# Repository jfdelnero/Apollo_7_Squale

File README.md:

Apollo 7 Squale toolchain and demos  
(c) 2015-2019 Jean-François DEL NERO  
(c) 2015-2019 Association MO5.COM ( [https://mo5.com](https://mo5.com) )
---

gcc6809 based Apollo 7 Squale C toolchain and demos examples

[Squale computer technical page](http://hxc2001.free.fr/Squale/index.html)

[Squale Demo release news letter](http://mag.mo5.com/actu/172742/mo5-com-presente-la-toute-premiere-demo-sur-squale)

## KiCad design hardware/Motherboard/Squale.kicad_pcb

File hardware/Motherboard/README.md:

Apollo 7 Squale Schematic and PCB 
---

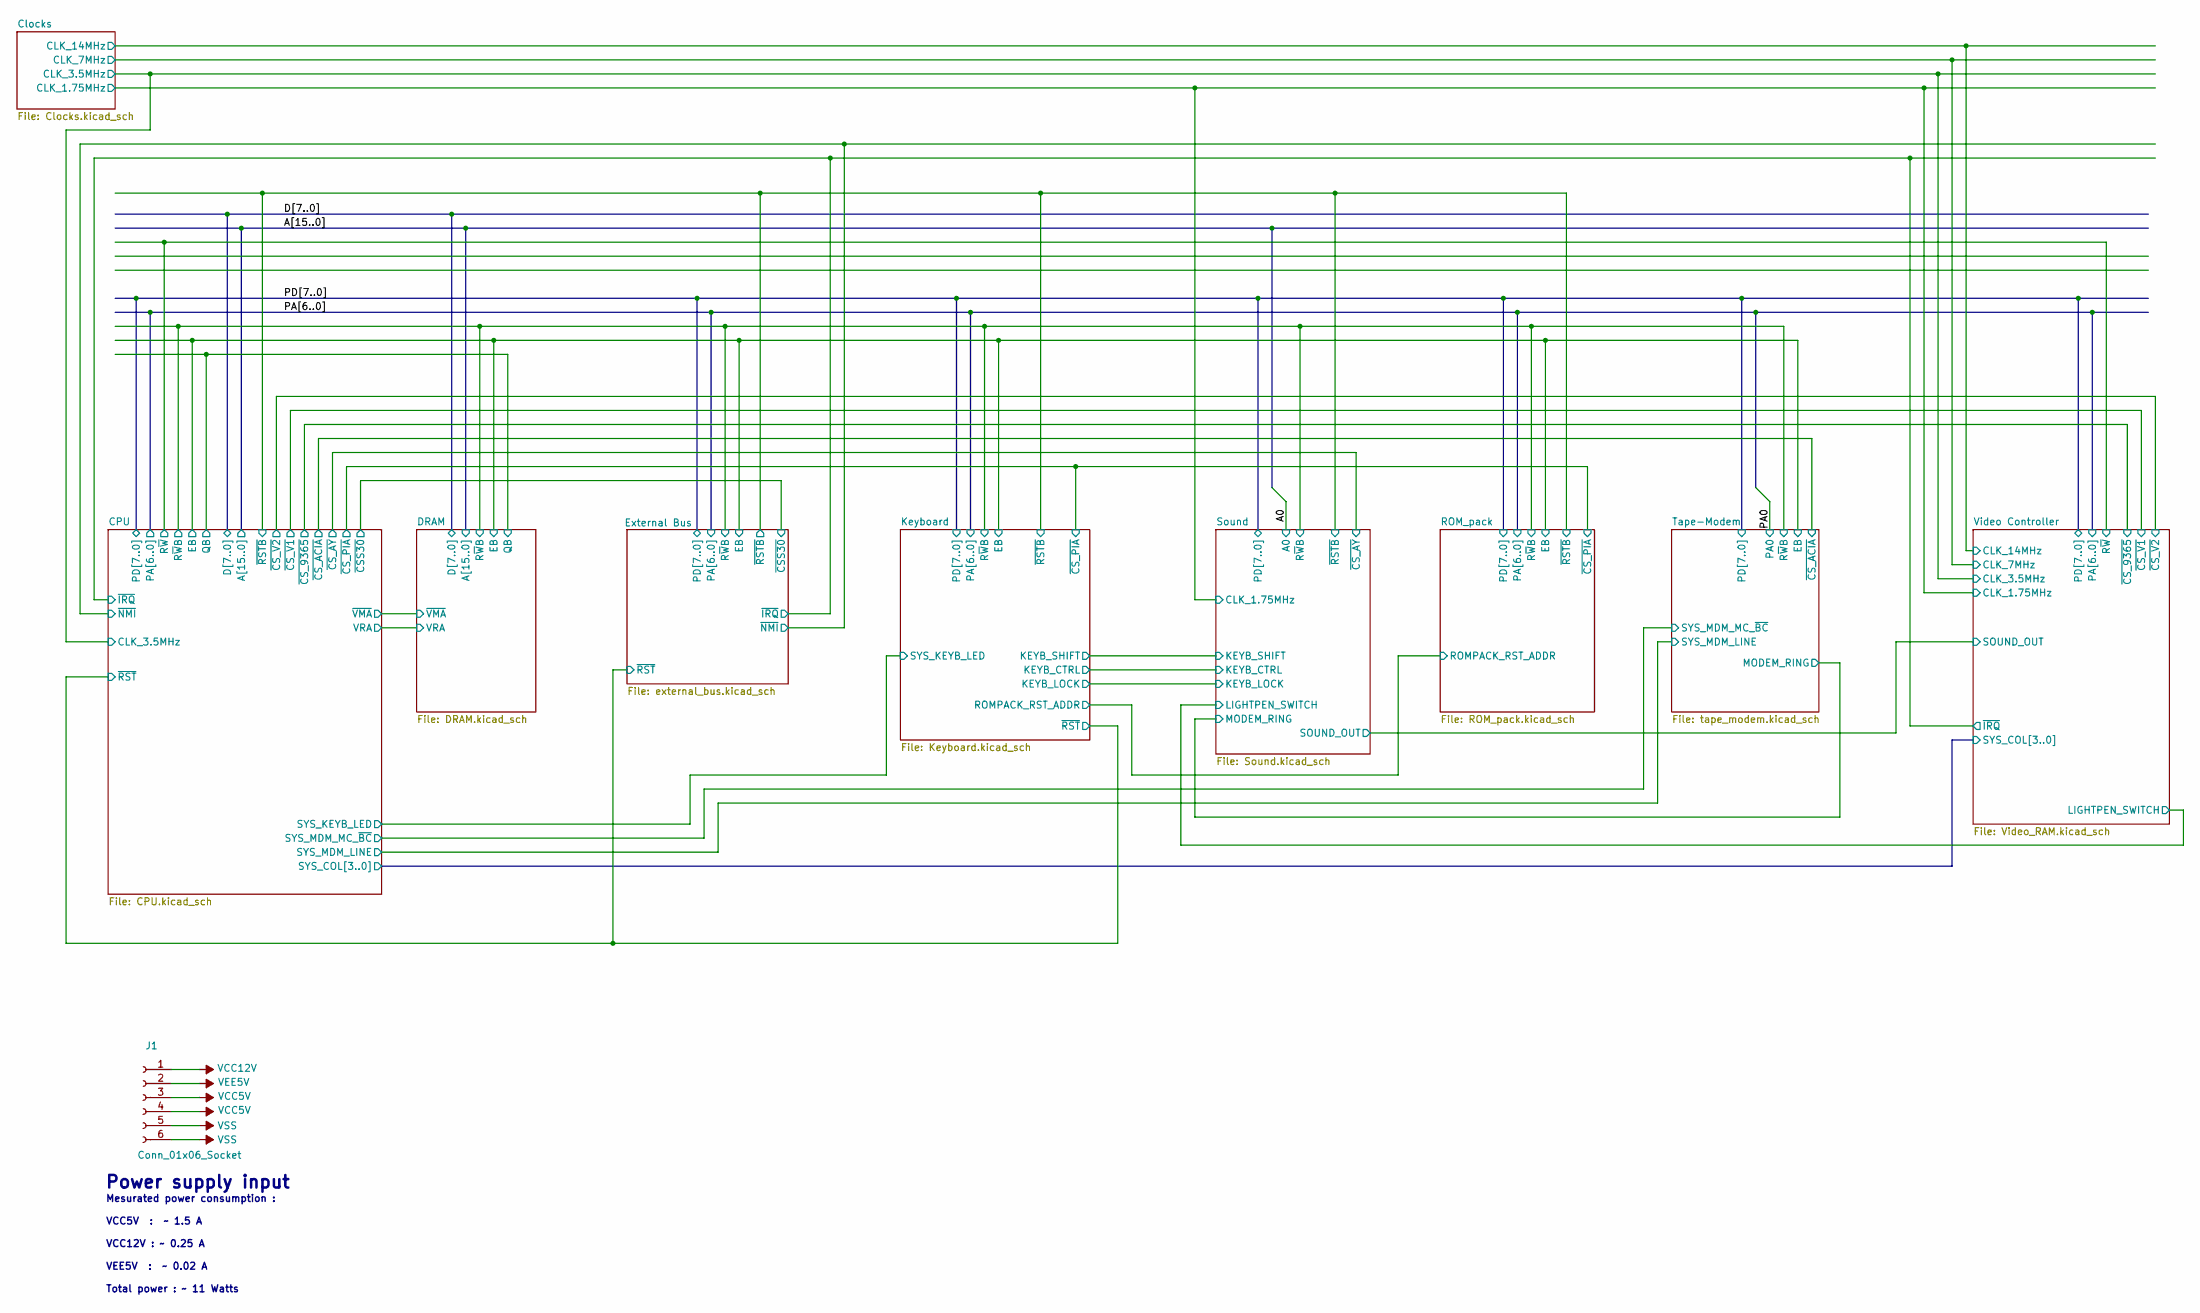
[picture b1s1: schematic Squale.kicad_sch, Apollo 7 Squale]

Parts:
J1: Conn_01x06_Socket; TerminalBlock_CUI_TB007-508-06_1x06_P5.08mm_Horizontal

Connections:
VCC5V: J1.3, J1.4; also elsewhere on the board
VCC12V: J1.1; also elsewhere on the board
VEE5V: J1.2; also elsewhere on the board
VSS: J1.5, J1.6; also elsewhere on the board

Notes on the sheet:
Power supply input
Mesurated power consumption : VCC5V : ~ 1.5 A VCC12V : ~ 0.25 A VEE5V : ~ 0.02 A Total power : ~ 11 Watts

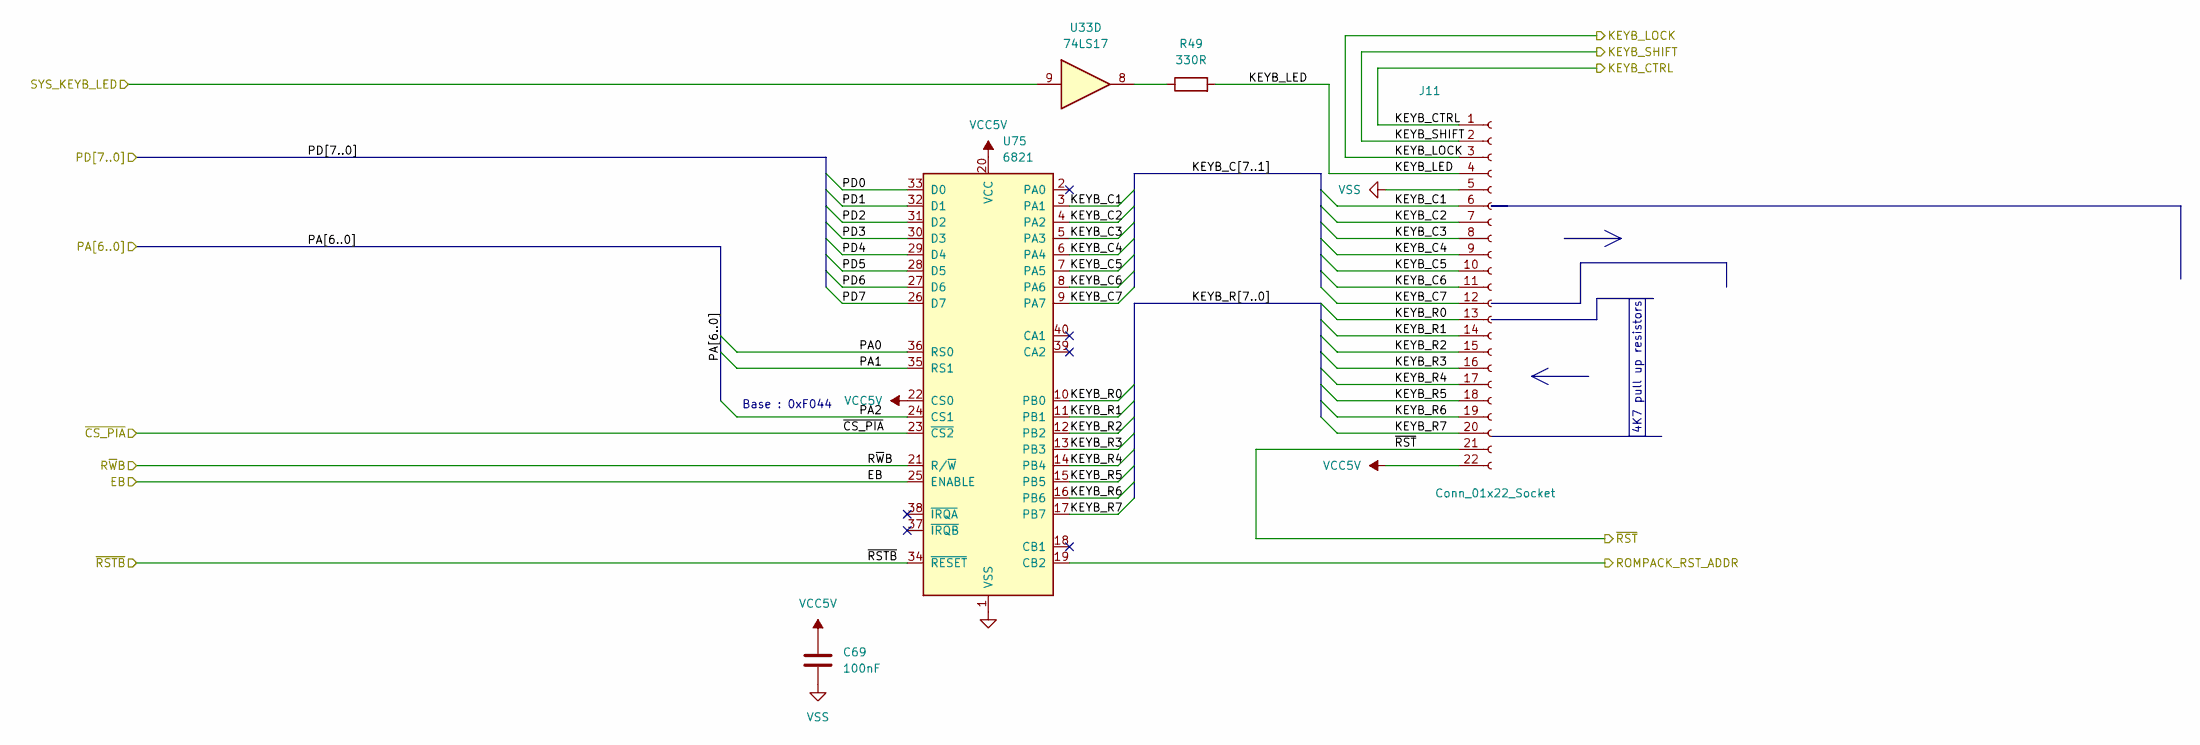
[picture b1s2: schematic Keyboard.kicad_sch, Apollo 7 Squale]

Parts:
C69: 100nF; C_Disc_D9.0mm_W2.5mm_P5.00mm
J11: Conn_01x22_Socket; PinHeader_1x22_P2.54mm_Vertical
R49: 330R; R_Axial_DIN0309_L9.0mm_D3.2mm_P12.70mm_Horizontal
U33: 74LS17; DIP-14_W7.62mm_Socket
U75: 6821; DIP-40_W15.24mm_Socket

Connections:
/CPU/EB: U75.25 (ENABLE); also elsewhere on the board
/CPU/R~WB: U75.21 (R/~W); also elsewhere on the board
/CPU/SYS_KEYB_LED: U33.9; also elsewhere on the board
/CPU/~CS_PIA: U75.23 (~CS2); also elsewhere on the board
/CPU/~RST: J11.21; also elsewhere on the board
/Keyboard/KEYB_C1: J11.6, U75.3 (PA1)
/Keyboard/KEYB_C2: J11.7, U75.4 (PA2)
/Keyboard/KEYB_C3: J11.8, U75.5 (PA3)
/Keyboard/KEYB_C4: J11.9, U75.6 (PA4)
/Keyboard/KEYB_C5: J11.10, U75.7 (PA5)
/Keyboard/KEYB_C6: J11.11, U75.8 (PA6)
/Keyboard/KEYB_C7: J11.12, U75.9 (PA7)
/Keyboard/KEYB_CTRL: J11.1; also elsewhere on the board
/Keyboard/KEYB_LED: J11.4, R49.2
/Keyboard/KEYB_LOCK: J11.3; also elsewhere on the board
/Keyboard/KEYB_R0: J11.13, U75.10 (PB0)
/Keyboard/KEYB_R1: J11.14, U75.11 (PB1)
/Keyboard/KEYB_R2: J11.15, U75.12 (PB2)
/Keyboard/KEYB_R3: J11.16, U75.13 (PB3)
/Keyboard/KEYB_R4: J11.17, U75.14 (PB4)
/Keyboard/KEYB_R5: J11.18, U75.15 (PB5)
/Keyboard/KEYB_R6: J11.19, U75.16 (PB6)
/Keyboard/KEYB_R7: J11.20, U75.17 (PB7)
/Keyboard/KEYB_SHIFT: J11.2; also elsewhere on the board
/Keyboard/ROMPACK_RST_ADDR: U75.19 (CB2); also elsewhere on the board
/Keyboard/~RSTB: U75.34 (~RESET); also elsewhere on the board
/PA0: U75.36 (RS0); also elsewhere on the board
/PA1: U75.35 (RS1); also elsewhere on the board
/PA2: U75.24 (CS1); also elsewhere on the board
/PD0: U75.33 (D0); also elsewhere on the board
/PD1: U75.32 (D1); also elsewhere on the board
/PD2: U75.31 (D2); also elsewhere on the board
/PD3: U75.30 (D3); also elsewhere on the board
/PD4: U75.29 (D4); also elsewhere on the board
/PD5: U75.28 (D5); also elsewhere on the board
/PD6: U75.27 (D6); also elsewhere on the board
/PD7: U75.26 (D7); also elsewhere on the board
unnamed: R49.1, U33.8
VCC5V: C69.1, J11.22, U75.20 (VCC), U75.22 (CS0); also elsewhere on the board
VSS: C69.2, J11.5, U75.1 (VSS); also elsewhere on the board

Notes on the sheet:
4K7 pull up resistors
Base : 0xF044

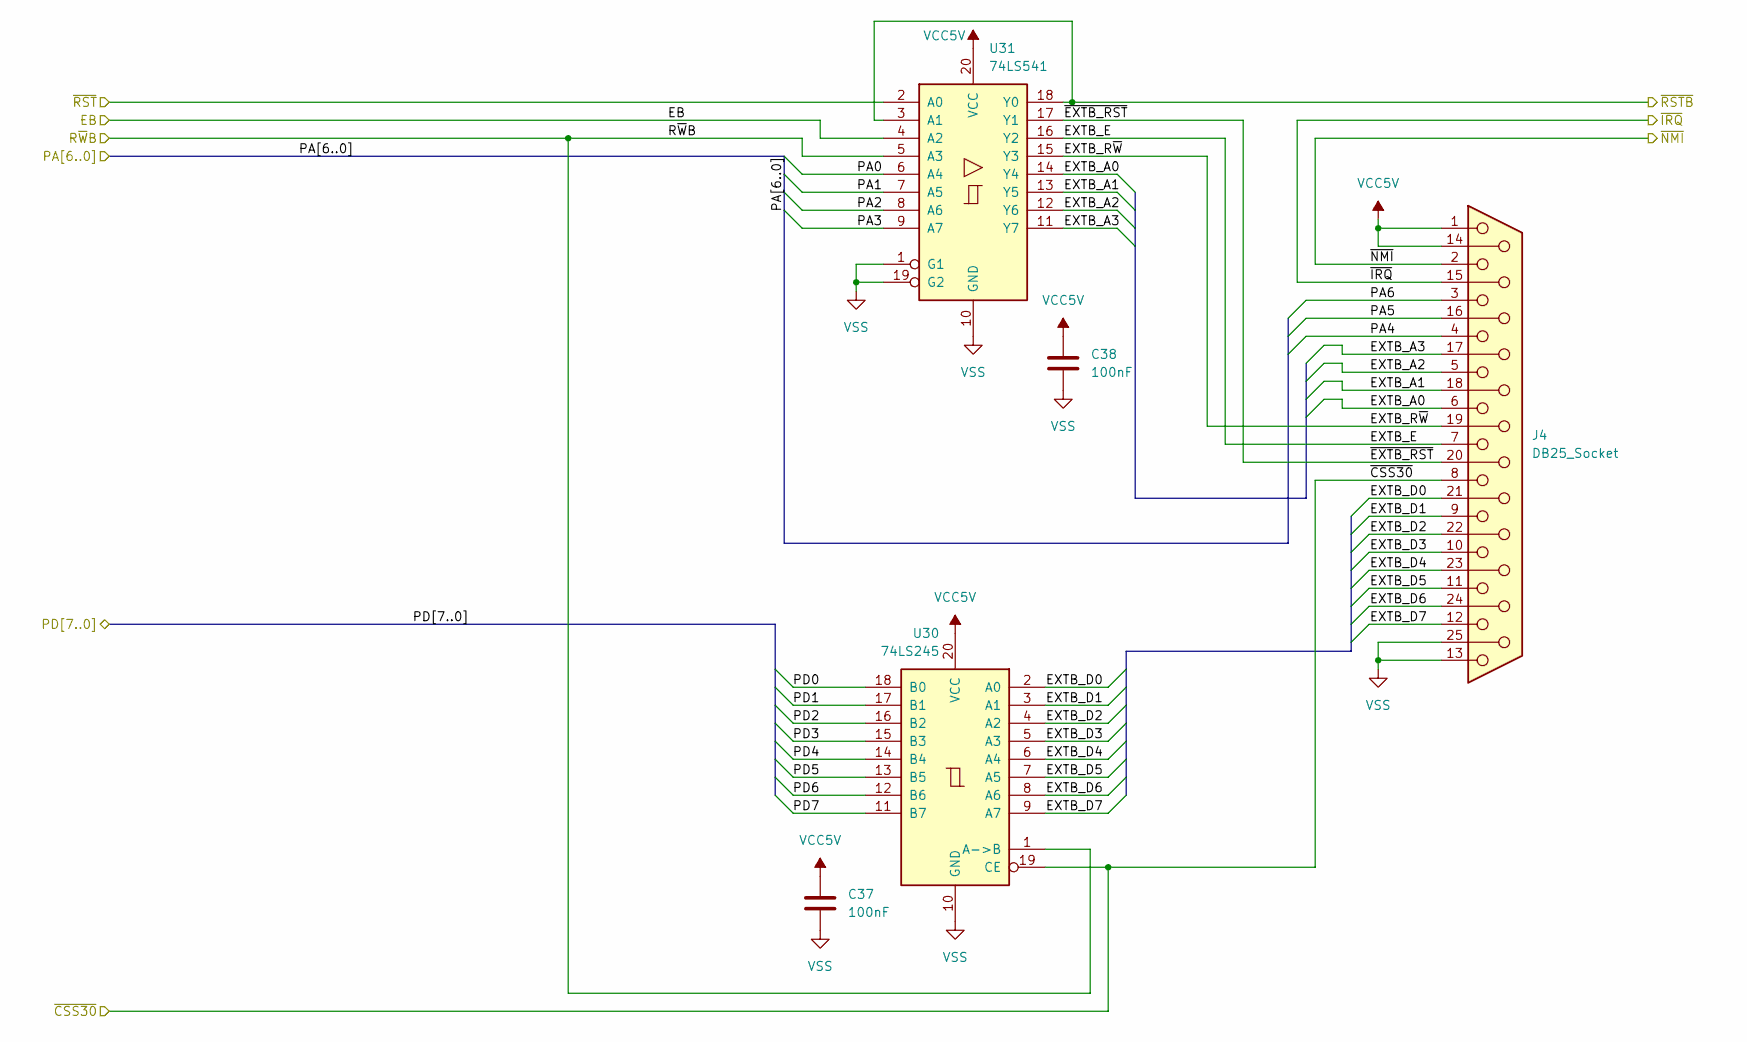
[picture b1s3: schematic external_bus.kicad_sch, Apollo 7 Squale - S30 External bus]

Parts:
C37, C38: 100nF; C_Disc_D9.0mm_W2.5mm_P5.00mm
J4: DB25_Socket; DSUB-25_Pins_Horizontal_P2.77x2.54mm_EdgePinOffset9.40mm
U30: 74LS245; DIP-20_W7.62mm_Socket
U31: 74LS541; DIP-20_W7.62mm_Socket

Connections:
/CPU/EB: U31.4 (A2); also elsewhere on the board
/CPU/R~WB: U30.1 (A->B), U31.5 (A3); also elsewhere on the board
/CPU/~CSS30: J4.8, U30.19 (CE); also elsewhere on the board
/CPU/~IRQ: J4.15; also elsewhere on the board
/CPU/~NMI: J4.2; also elsewhere on the board
/CPU/~RST: U31.2 (A0); also elsewhere on the board
/External Bus/EXTB_A0: J4.6, U31.14 (Y4)
/External Bus/EXTB_A1: J4.18, U31.13 (Y5)
/External Bus/EXTB_A2: J4.5, U31.12 (Y6)
/External Bus/EXTB_A3: J4.17, U31.11 (Y7)
/External Bus/EXTB_D0: J4.21, U30.2 (A0)
/External Bus/EXTB_D1: J4.9, U30.3 (A1)
/External Bus/EXTB_D2: J4.22, U30.4 (A2)
/External Bus/EXTB_D3: J4.10, U30.5 (A3)
/External Bus/EXTB_D4: J4.23, U30.6 (A4)
/External Bus/EXTB_D5: J4.11, U30.7 (A5)
/External Bus/EXTB_D6: J4.24, U30.8 (A6)
/External Bus/EXTB_D7: J4.12, U30.9 (A7)
/External Bus/EXTB_E: J4.7, U31.16 (Y2)
/External Bus/EXTB_R~W: J4.19, U31.15 (Y3)
/External Bus/~EXTB_RST: J4.20, U31.17 (Y1)
/Keyboard/~RSTB: U31.3 (A1), U31.18 (Y0); also elsewhere on the board
/PA0: U31.6 (A4); also elsewhere on the board
/PA1: U31.7 (A5); also elsewhere on the board
/PA2: U31.8 (A6); also elsewhere on the board
/PA3: U31.9 (A7); also elsewhere on the board
/PA4: J4.4; also elsewhere on the board
/PA5: J4.16; also elsewhere on the board
/PA6: J4.3; also elsewhere on the board
/PD0: U30.18 (B0); also elsewhere on the board
/PD1: U30.17 (B1); also elsewhere on the board
/PD2: U30.16 (B2); also elsewhere on the board
/PD3: U30.15 (B3); also elsewhere on the board
/PD4: U30.14 (B4); also elsewhere on the board
/PD5: U30.13 (B5); also elsewhere on the board
/PD6: U30.12 (B6); also elsewhere on the board
/PD7: U30.11 (B7); also elsewhere on the board
VCC5V: C37.1, C38.1, J4.1, J4.14, U30.20 (VCC), U31.20 (VCC); also elsewhere on the board
VSS: C37.2, C38.2, J4.13, J4.25, U30.10 (GND), U31.1 (G1), U31.10 (GND), U31.19 (G2); also elsewhere on the board

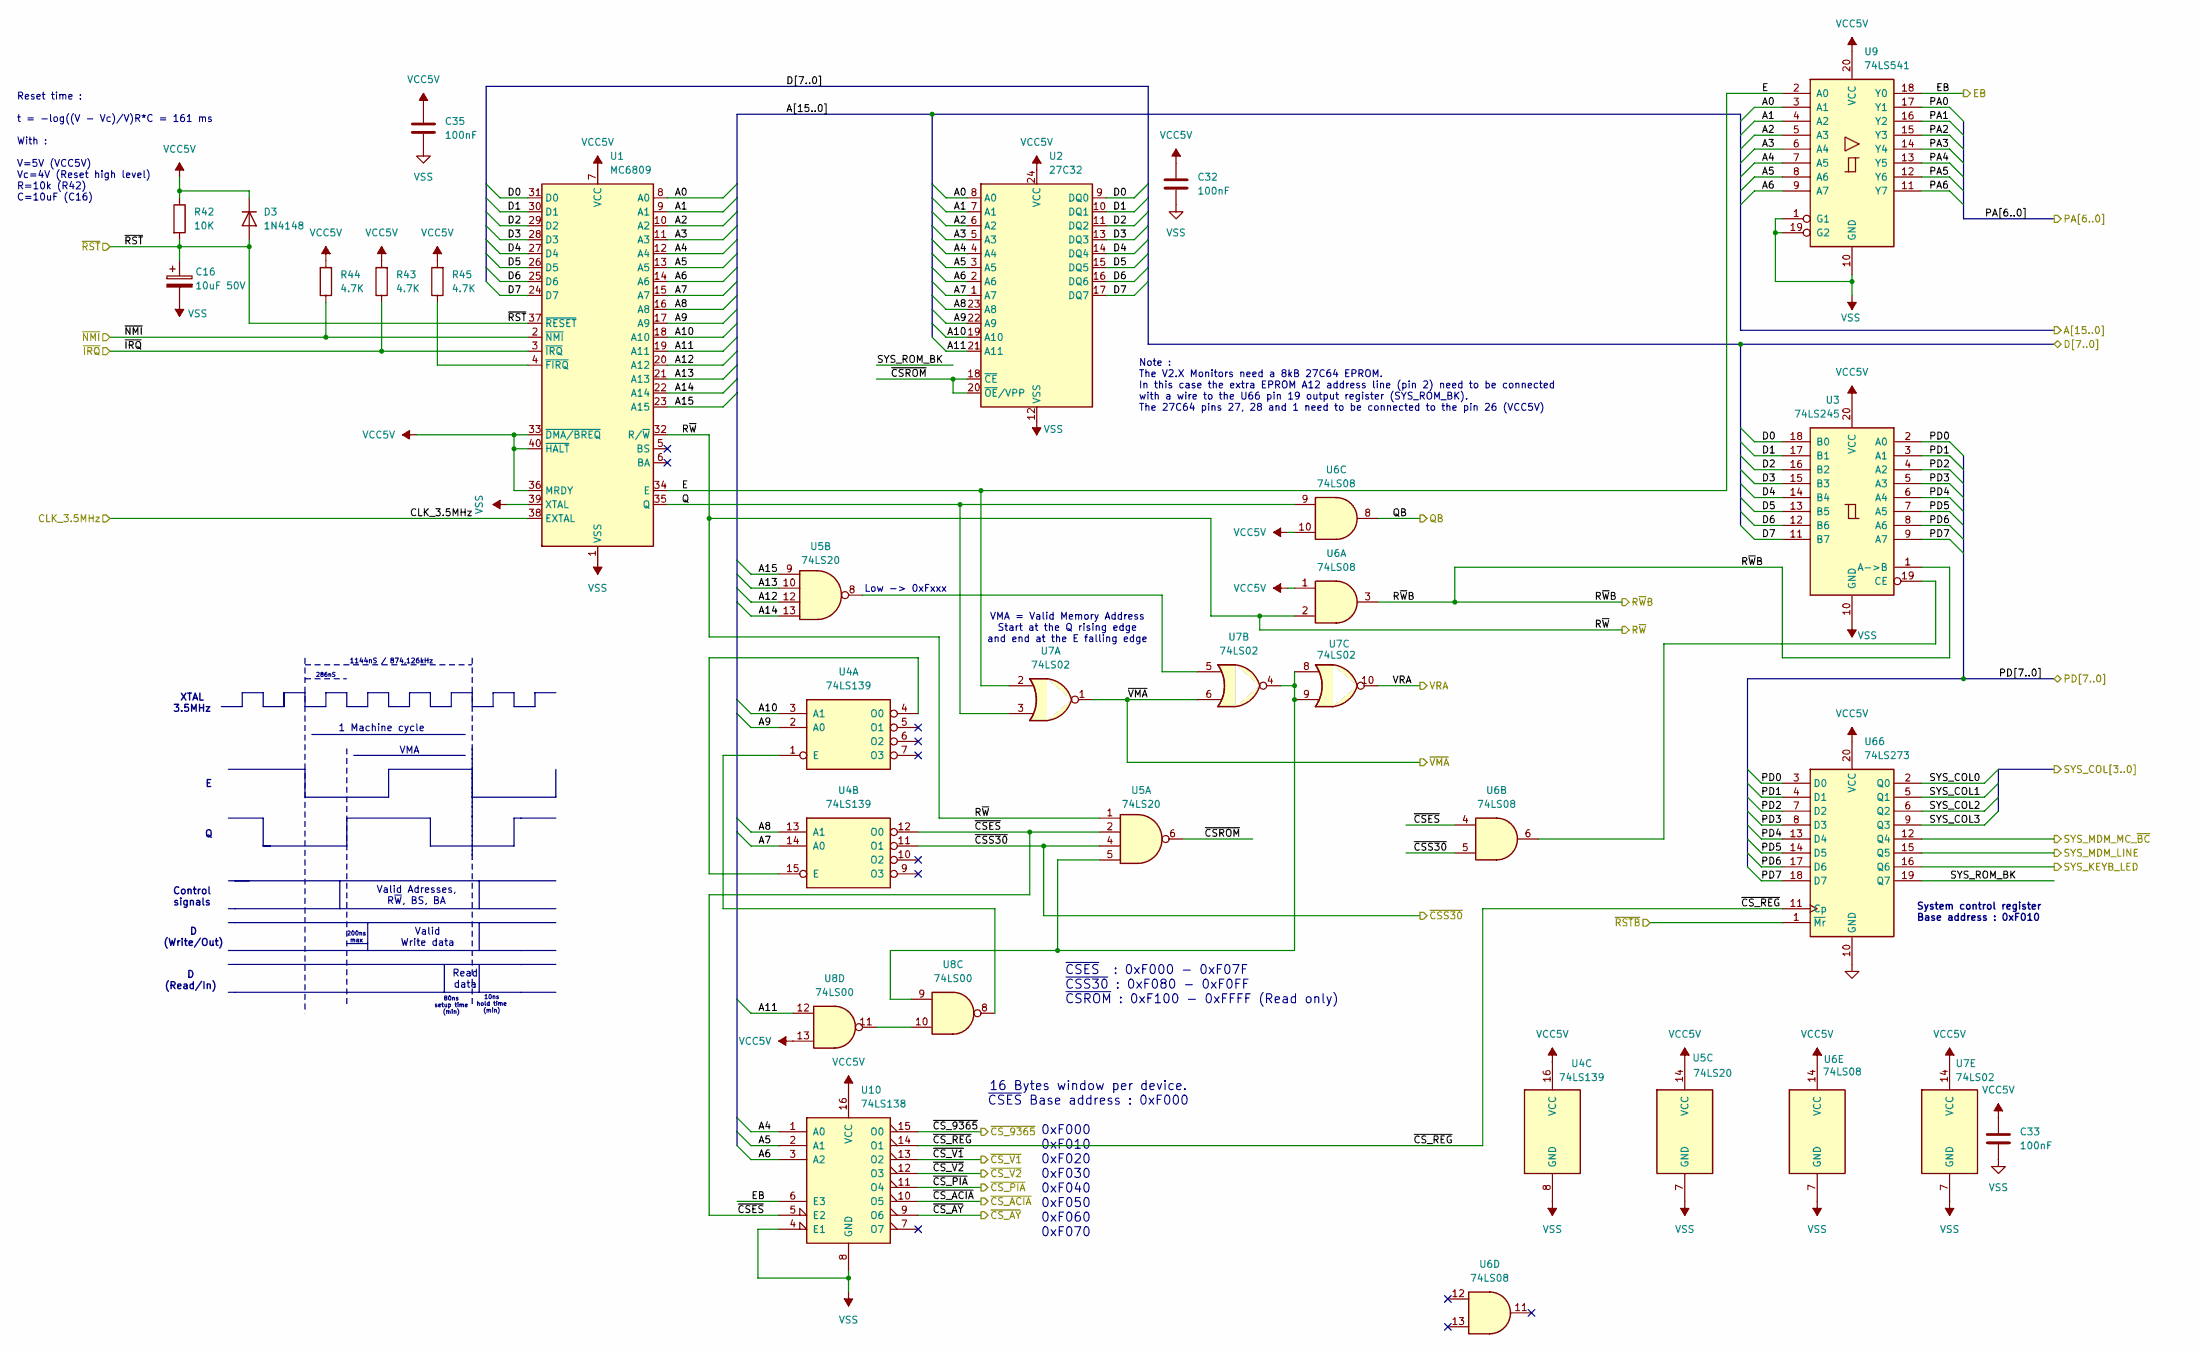
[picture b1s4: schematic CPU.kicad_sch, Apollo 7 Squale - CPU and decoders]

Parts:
C16: 10uF 50V; C_Radial_D6.3mm_H5.0mm_P2.50mm
C32, C33, C35: 100nF; C_Disc_D9.0mm_W2.5mm_P5.00mm
D3: 1N4148; D_DO-35_SOD27_P12.70mm_Horizontal
R42: 10K; R_Axial_DIN0309_L9.0mm_D3.2mm_P12.70mm_Horizontal
R43, R44, R45: 4.7K; R_Axial_DIN0309_L9.0mm_D3.2mm_P12.70mm_Horizontal
U1: MC6809; DIP-40_W15.24mm_Socket
U2: 27C32; DIP-24_W15.24mm_Socket
U3: 74LS245; DIP-20_W7.62mm_Socket
U4: 74LS139; DIP-16_W7.62mm_Socket
U5: 74LS20; DIP-14_W7.62mm_Socket
U6: 74LS08; DIP-14_W7.62mm_Socket
U7: 74LS02; DIP-14_W7.62mm_Socket
U8: 74LS00; DIP-14_W7.62mm_Socket
U9: 74LS541; DIP-20_W7.62mm_Socket
U10: 74LS138; DIP-16_W7.62mm_Socket
U66: 74LS273; DIP-20_W7.62mm_Socket

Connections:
/A0: U1.8 (A0), U2.8 (A0), U9.3 (A1); also elsewhere on the board
/A1: U1.9 (A1), U2.7 (A1), U9.4 (A2); also elsewhere on the board
/A2: U1.10 (A2), U2.6 (A2), U9.5 (A3); also elsewhere on the board
/A3: U1.11 (A3), U2.5 (A3), U9.6 (A4); also elsewhere on the board
/A4: U1.12 (A4), U2.4 (A4), U9.7 (A5), U10.1 (A0); also elsewhere on the board
/A5: U1.13 (A5), U2.3 (A5), U9.8 (A6), U10.2 (A1); also elsewhere on the board
/A6: U1.14 (A6), U2.2 (A6), U9.9 (A7), U10.3 (A2); also elsewhere on the board
/A7: U1.15 (A7), U2.1 (A7), U4.14 (A0); also elsewhere on the board
/A8: U1.16 (A8), U2.23 (A8), U4.13 (A1); also elsewhere on the board
/A9: U1.17 (A9), U2.22 (A9), U4.2 (A0); also elsewhere on the board
/A10: U1.18 (A10), U2.19 (A10), U4.3 (A1); also elsewhere on the board
/A11: U1.19 (A11), U2.21 (A11), U8.12; also elsewhere on the board
/A12: U1.20 (A12), U5.12; also elsewhere on the board
/A13: U1.21 (A13), U5.10; also elsewhere on the board
/A14: U1.22 (A14), U5.13; also elsewhere on the board
/A15: U1.23 (A15), U5.9; also elsewhere on the board
/CPU/CLK_3.5MHz: U1.38 (EXTAL); also elsewhere on the board
/CPU/E: U1.34 (E), U7.2, U9.2 (A0)
/CPU/EB: U9.18 (Y0), U10.6 (E3); also elsewhere on the board
/CPU/Q: U1.35 (Q), U6.9, U7.3
/CPU/QB: U6.8; also elsewhere on the board
/CPU/R~W: U1.32 (R/~W), U5.1, U6.2; also elsewhere on the board
/CPU/R~WB: U3.1 (A->B), U6.3; also elsewhere on the board
/CPU/SYS_KEYB_LED: U66.16 (Q6); also elsewhere on the board
/CPU/SYS_ROM_BK: U66.19 (Q7)
/CPU/VRA: U7.10; also elsewhere on the board
/CPU/~CSES: U4.12 (O0), U5.2, U6.4, U10.5 (E2)
/CPU/~CSROM: U2.18 (~CE), U2.20 (~OE/VPP), U5.6
/CPU/~CSS30: U4.11 (O1), U5.4, U6.5; also elsewhere on the board
/CPU/~CS_9365: U10.15 (O0); also elsewhere on the board
/CPU/~CS_ACIA: U10.10 (O5); also elsewhere on the board
/CPU/~CS_AY: U10.9 (O6); also elsewhere on the board
/CPU/~CS_PIA: U10.11 (O4); also elsewhere on the board
/CPU/~CS_REG: U10.14 (O1), U66.11 (Cp)
/CPU/~CS_V1: U10.13 (O2); also elsewhere on the board
/CPU/~CS_V2: U10.12 (O3); also elsewhere on the board
/CPU/~IRQ: R43.1, U1.3 (~IRQ); also elsewhere on the board
/CPU/~NMI: R44.1, U1.2 (~NMI); also elsewhere on the board
/CPU/~RST: C16.1, D3.2 (A), R42.2, U1.37 (~RESET); also elsewhere on the board
/CPU/~VMA: U7.1, U7.6; also elsewhere on the board
/D0: U1.31 (D0), U2.9 (DQ0), U3.18 (B0); also elsewhere on the board
/D1: U1.30 (D1), U2.10 (DQ1), U3.17 (B1); also elsewhere on the board
/D2: U1.29 (D2), U2.11 (DQ2), U3.16 (B2); also elsewhere on the board
/D3: U1.28 (D3), U2.13 (DQ3), U3.15 (B3); also elsewhere on the board
/D4: U1.27 (D4), U2.14 (DQ4), U3.14 (B4); also elsewhere on the board
/D5: U1.26 (D5), U2.15 (DQ5), U3.13 (B5); also elsewhere on the board
/D6: U1.25 (D6), U2.16 (DQ6), U3.12 (B6); also elsewhere on the board
/D7: U1.24 (D7), U2.17 (DQ7), U3.11 (B7); also elsewhere on the board
/Keyboard/~RSTB: U66.1 (~Mr); also elsewhere on the board
/PA0: U9.17 (Y1); also elsewhere on the board
/PA1: U9.16 (Y2); also elsewhere on the board
/PA2: U9.15 (Y3); also elsewhere on the board
/PA3: U9.14 (Y4); also elsewhere on the board
/PA4: U9.13 (Y5); also elsewhere on the board
/PA5: U9.12 (Y6); also elsewhere on the board
/PA6: U9.11 (Y7); also elsewhere on the board
/PD0: U3.2 (A0), U66.3 (D0); also elsewhere on the board
/PD1: U3.3 (A1), U66.4 (D1); also elsewhere on the board
/PD2: U3.4 (A2), U66.7 (D2); also elsewhere on the board
/PD3: U3.5 (A3), U66.8 (D3); also elsewhere on the board
/PD4: U3.6 (A4), U66.13 (D4); also elsewhere on the board
/PD5: U3.7 (A5), U66.14 (D5); also elsewhere on the board
/PD6: U3.8 (A6), U66.17 (D6); also elsewhere on the board
/PD7: U3.9 (A7), U66.18 (D7); also elsewhere on the board
/Tape-Modem/SYS_MDM_LINE: U66.15 (Q5); also elsewhere on the board
/Tape-Modem/SYS_MDM_MC_~BC: U66.12 (Q4); also elsewhere on the board
/Video Controller/SYS_COL0: U66.2 (Q0); also elsewhere on the board
/Video Controller/SYS_COL1: U66.5 (Q1); also elsewhere on the board
/Video Controller/SYS_COL2: U66.6 (Q2); also elsewhere on the board
/Video Controller/SYS_COL3: U66.9 (Q3); also elsewhere on the board
unnamed: R45.1, U1.4 (~FIRQ)
unnamed: U3.19 (CE), U6.6
unnamed: U4.1 (E), U8.8
unnamed: U4.4 (O0), U4.15 (E)
unnamed: U5.5, U7.4, U7.8, U7.9, U8.9
unnamed: U5.8, U7.5
unnamed: U8.10, U8.11
VCC5V: C32.1, C33.1, C35.1, D3.1 (K), R42.1, R43.2, R44.2, R45.2, U1.7 (VCC), U1.33 (~DMA/BREQ), U1.36 (MRDY), U1.40 (~HALT), U2.24 (VCC), U3.20 (VCC), U4.16 (VCC), U5.14 (VCC), U6.1, U6.10, U6.14 (VCC), U7.14 (VCC), U8.13, U9.20 (VCC), U10.16 (VCC), U66.20 (VCC); also elsewhere on the board
VSS: C16.2, C32.2, C33.2, C35.2, U1.1 (VSS), U1.39 (XTAL), U2.12 (VSS), U3.10 (GND), U4.8 (GND), U5.7 (GND), U6.7 (GND), U7.7 (GND), U9.1 (G1), U9.10 (GND), U9.19 (G2), U10.4 (E1), U10.8 (GND), U66.10 (GND); also elsewhere on the board

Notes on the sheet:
Note : The V2.X Monitors need a 8kB 27C64 EPROM. In this case the extra EPROM A12 address line (pin 2) need to be connected with a wire to the U66 pin 19 output register (SYS_ROM_BK). The 27C64 pins 27, 28 and 1 need to be connected to the pin 26 (VCC5V)
0xF000 0xF010 0xF020 0xF030 0xF040 0xF050 0xF060 0xF070
Low -> 0xFxxx
200ns max
286nS
16 Bytes window per device. ~{CSES} Base address : 0xF000
~{CSES} : 0xF000 - 0xF07F ~{CSS30} : 0xF080 - 0xF0FF ~{CSROM} : 0xF100 - 0xFFFF (Read only)
Valid Write data
Read data
Control signals
Valid Adresses, R~{W}, BS, BA
1 Machine cycle
VMA
Reset time : t = -log((V - Vc)/V)R*C = 161 ms With : V=5V (VCC5V) Vc=4V (Reset high level) R=10k (R42) C=10uF (C16)
D (Write/Out)
10ns hold time (min)
VMA = Valid Memory Address Start at the Q rising edge and end at the E falling edge
D (Read/In)
80ns setup time (min)
1144nS / 874,126kHz
System control register Base address : 0xF010
XTAL 3.5MHz

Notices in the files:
hardware/Motherboard/CPU.kicad_sch:
CC-BY Licence (Creative Commons Attribution)
